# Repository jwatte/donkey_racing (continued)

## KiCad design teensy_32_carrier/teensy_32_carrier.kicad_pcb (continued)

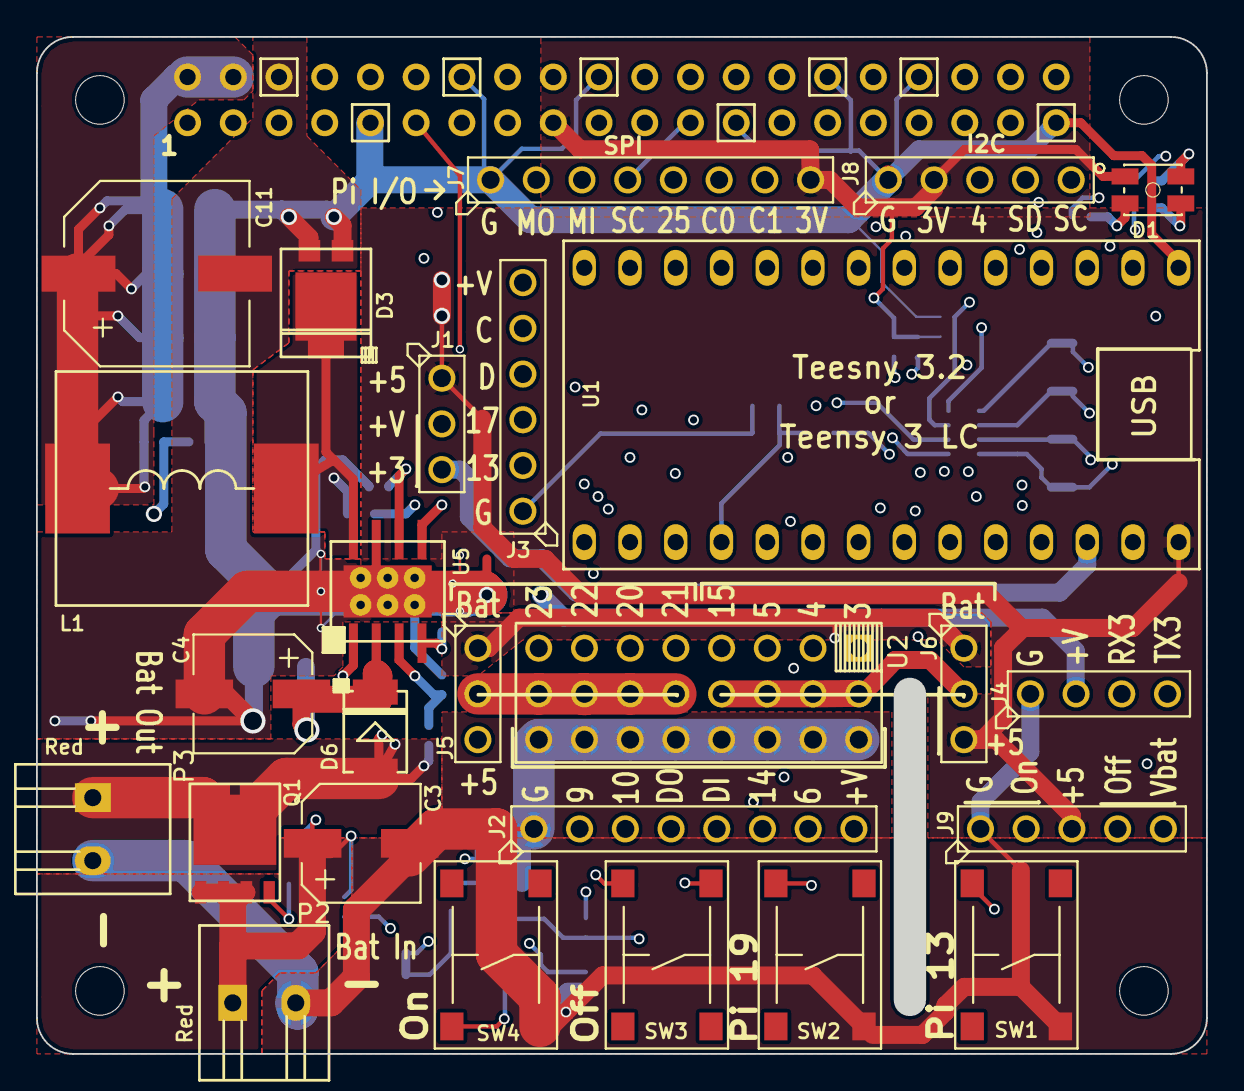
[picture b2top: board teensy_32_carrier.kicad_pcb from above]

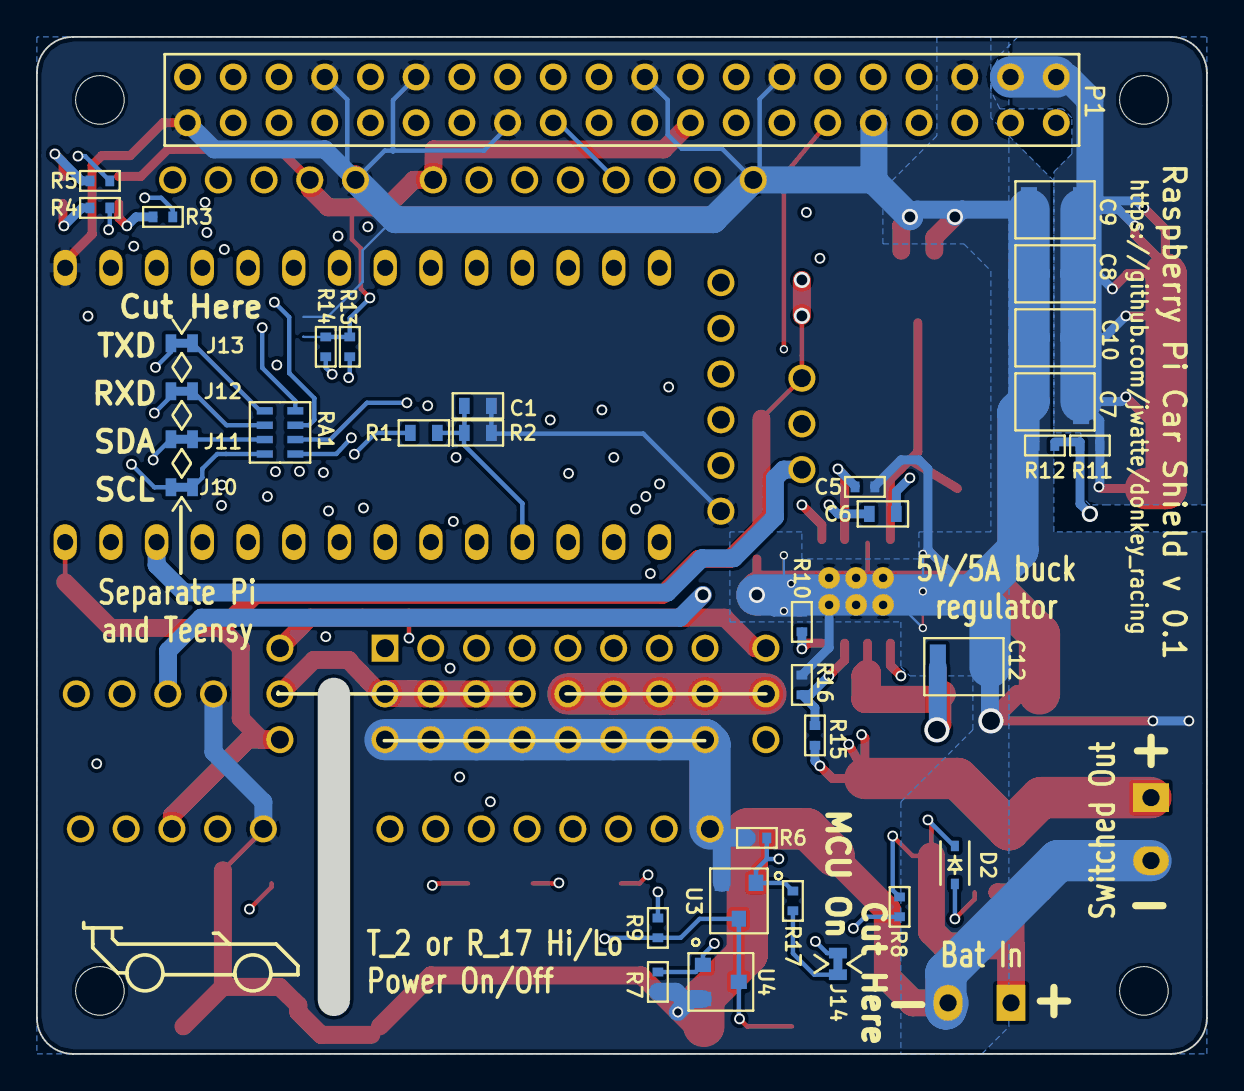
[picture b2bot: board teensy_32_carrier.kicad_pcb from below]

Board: 4 copper layers, 63.3 x 54.8 mm, 61 parts (35 on the bottom side), 67 nets.

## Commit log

2017-08-08 first commit -- create synthetic model to train on
2017-08-08 add README
2017-08-14 Add information about teensy board files
2017-08-14 add teensy carrier board schematic
2017-08-16 more parts in teensy lib
2017-08-17 first revision of teensy 3.2 carrier hat
2017-08-18 first batch of layout
2017-08-18 Update generated pdf files.
2017-08-18 Choose a part for screw terminals.
2017-08-18 set up design rules
2017-08-18 Add a simple ip_beacon tool to broadcast presence
2017-08-18 make a search mode, and wrap it in proper systemd mumbo-jumbo.
2017-08-18 pre routing
2017-08-18 start routing
2017-08-19 routing getting closer to first completion
2017-08-19 version 0.1 ready to test upload
2017-08-20 A Teensy sketch to read a receiver and write the ESC/steering
2017-08-20 prep for order v0.1
2017-08-20 improve the RC control; use serial channel data
2017-08-21 checkpoint before computer entirely dies
2017-08-21 progress on serial protocol handler
2017-08-22 make ip_beacon work better with systemd
2017-08-22 txt files probably shouldn't be ignored, after all
2017-08-22 progress on serial control
2017-08-22 serial comms compiles
2017-08-28 trying to fit an RTC and the Hat EEPROM, but no.
2017-08-28 start up pilot executable for rpi
2017-08-30 calibration scripts
2017-08-30 calibration script works
2017-08-30 actual working calibration
2017-08-30 more calibratioN
2017-08-31 build a network that might work
2017-08-31 progress towards trying to run a network
2017-09-01 I have a model that can train and infer.... I think?
2017-09-02 checkpoint that compiles
2017-09-02 time the current NN to 72 milliseconds
2017-09-03 start on the design manifest and protocol definition
2017-09-03 fix some inconsistencies
2017-09-03 improve protocol
2017-09-03 document and update calibrate_camera; make it generate CPP tables
2017-09-03 Make pilot spin up the camera capture
2017-09-03 make the network smaller, to run faster.
2017-09-04 framework that can unwarp and forward a frame for processing
2017-09-04 GUI uploads texture data
2017-09-05 display rectified textures, and metrics
2017-09-05 attempt to work around Linux USB driver problems
2017-09-07 user RawHID, not serial
2017-09-07 prepare to record driving+video
2017-09-07 more readiness to record images
2017-09-08 look slightly further ahead
2017-09-08 start figuring out how to make training data from video+telemetry
2017-09-09 rename mktrain
2017-09-09 update file names
2017-09-09 checkpoint
2017-09-10 progress towards training
2017-09-11 start to train network
2017-09-12 whipped into shape at which point it learns
2017-09-14 version 2 macrofab project
2017-09-16 prepare to load network in C++
2017-09-16 save to crunk files
2017-09-16 update training
2017-09-16 patch to record at race
2017-09-28 build better database
2017-09-28 go longer
2017-09-28 improve segment capture
2017-09-28 improve calibration code
2017-09-28 use a larger area of input data
2017-09-29 support longer training runs
2017-09-29 a newer topology, and generate database using CV labeling
2017-10-01 factor out net building
2017-10-04 finally, a model that works; uoptionally se CV for labeling
2017-10-08 better CV solution, and permute the image input order
2017-10-13 start modifying to grayscale texture size
2017-10-14 create network instance
2017-10-15 better visualization
2017-10-15 yet another network model
2017-10-15 make network work
2017-10-15 remove unused crap
2017-10-15 closer to driving
2017-10-16 try to debug power
2017-10-16 attempt to funnel data from A to B
2017-10-17 console
2017-10-17 clean up temp folder a bit. also add some metrics, chasing the gui performance problem
2017-10-17 everything is slow?
2017-10-17 back up to before double data buffers -- still mysteriously slow
2017-10-19 debug low framerate
2017-10-20 asynchronize file writing. make sure steering gets through to board. tweak GUI
2017-10-20 also flush on keyframes
2017-10-21 ready to race?
2017-10-21 update for reverse Hitec servo
2017-10-21 network for racing
2017-10-22 don't clean up if there's plenty of space
2017-10-22 logging to file through cmdline arg
2017-10-22 make image more sensitive to yellow
2017-10-22 param for tweaking steering
2017-10-22 print less verbose classification
2017-10-22 don't check in the reset tool
2017-10-22 remove a hard-coded offset
2017-10-22 train shorter
2017-10-22 compensate for light
2017-10-28 new Pi shield
2017-10-29 move forward on new hat
2017-10-29 carrier update
2017-10-29 update calibrate
2017-10-29 update capture / calibrate
2017-10-30 power regulator for hat
2017-10-30 schematic tweaks
2017-10-31 more hat
2017-11-02 try to make flat map
2017-11-02 seems to work now?
2017-11-10 progress on new hat
2017-11-13 attempt to project top-down -- somewhat OK
2017-11-13 better top-down projection
2017-11-13 new 146x146 network
2017-11-14 make area of detect wider, and adjust to actual image dimensions
2017-11-18 square top-down, orange cone detection
2017-11-18 larger chunks; attempt to better detect taps
2017-11-18 gallery minor tweaks
2017-11-26 start refactoring pilot UI
2017-11-26 slight tweak to throttle values.
2017-11-27 another attempt at Hat layout -- pre routing
2017-11-27 Macrofab proto order of teensy hat v2b
2017-12-29 teensy fw for hat
2017-12-30 Teensy 3.2 (and Teensy LC) compatible firmware.
2017-12-30 update teensy hat schematic
2017-12-30 Allow programming while keeping power on, and report time since received data, and use Serial1 for iBus.
2017-12-31 changes before nuking
2017-12-31 version 2017-12-30 of hat
2017-12-31 update footprint for MOSFET
2017-12-31 make I2C/RPiUART port supply 3V.
2018-01-02 tvs/zener protections
2018-01-07 revert to non-merge-conflict calibrate
2018-01-07 updated hat firmware
2018-01-07 more work on teensy shield
2018-01-07 update to python 3
2018-01-07 152x40 rectification
2018-01-07 new network topology
2018-01-08 more misc dev
2018-01-09 new size of image
2018-01-15 cut slimmer rectangle from camera
2018-01-15 teensy hat updates
2018-01-17 bigger output image
2018-01-20 Fix I2C PCA9685 emulation. Increase I2C idle timeout.
2018-01-20 don't drive backwards if in safe mode
2018-01-20 fix protocol bugs
2018-01-23 make I2C work even without RC dead man's grip
2018-01-23 test sketch that just sends I2C -> PWM
2018-01-23 smaller speed range on test
2018-02-03 crop more above horizon
2018-02-19 Document the hat project
2018-02-19 Updates to hat for next manufacturing run (pre order)
    remove unused directories
    move over teensy3.lib library that was needed
2018-02-23 prep for order
2018-02-24 tweaks to TVS diodes and board outline slot
2018-02-24 update documentation
2018-02-24 README update
2018-02-24 fix formatting in hat README
2018-03-11 update firmware to support reporting on demand
2018-03-16 Initial bang-out of VESC UART commands.
2018-03-17 Working VESC / FOCBOX support for the Teensy speed output.
2018-03-18 smooth out movements
2018-03-19 make a working flat-top table
2018-05-07 Make the message lamp blink fast when receiving instructions, slow when not.
2018-10-06 don't include VESC support by default
2018-10-07 add stb as submodule
2021-07-28 ripper-cleanup: save off changes
